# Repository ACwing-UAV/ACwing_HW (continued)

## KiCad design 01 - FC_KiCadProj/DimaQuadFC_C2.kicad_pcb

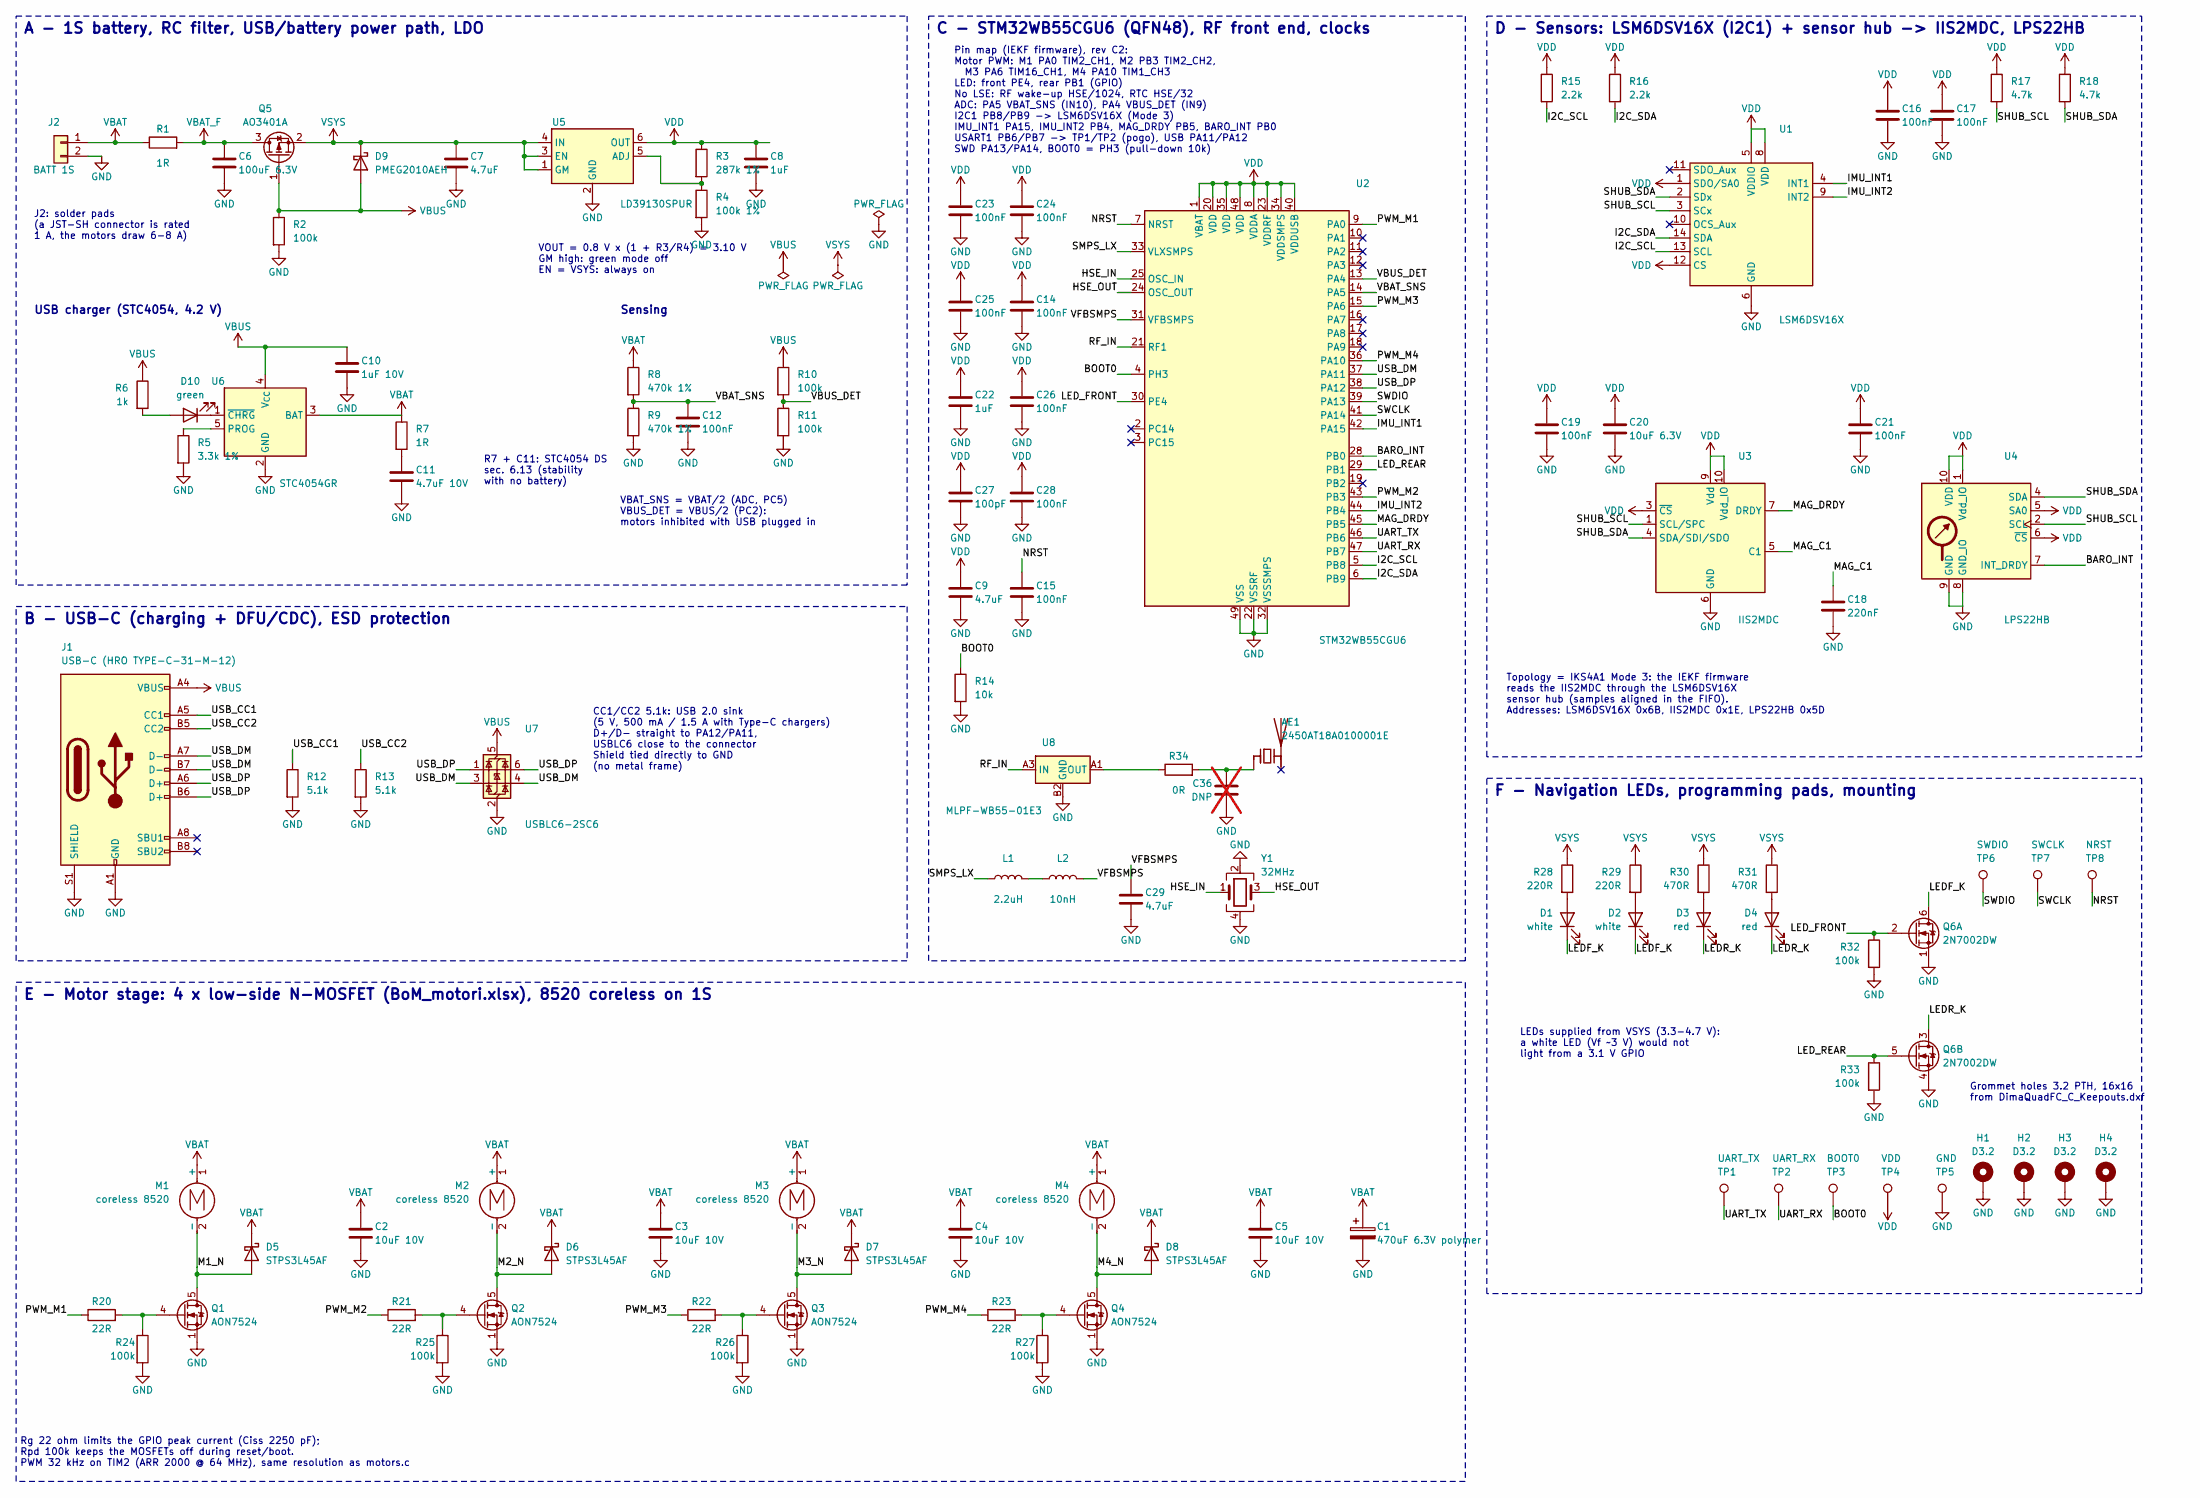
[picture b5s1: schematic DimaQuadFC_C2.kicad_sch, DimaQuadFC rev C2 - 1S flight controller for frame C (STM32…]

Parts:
AE1: 2450AT18A0100001E; Johanson_2450AT18x100
C1: 470uF 6.3V polymer; CP_EIA-7343-31_Kemet-D
C2, C3, C4, C5: 10uF 10V; C_0603_1608Metric
C6: 100uF 6.3V; C_1206_3216Metric
C7, C9: 4.7uF; C_0603_1608Metric
C8, C22: 1uF; C_0402_1005Metric
C10: 1uF 10V; C_0402_1005Metric
C11: 4.7uF 10V; C_0603_1608Metric
C12, C14, C15, C16, C17, C19, C21, C23, C24, C25, C26, C28: 100nF; C_0402_1005Metric
C18: 220nF; C_0402_1005Metric
C20: 10uF 6.3V; C_0603_1608Metric
C27: 100pF; C_0402_1005Metric
C29: 4.7uF; C_0402_1005Metric
C36: DNP; C_0402_1005Metric; not fitted
D1, D2: white; LED_0402_1005Metric
D3, D4: red; LED_0402_1005Metric
D5, D6, D7, D8: STPS3L45AF; D_SMAflat
D9: PMEG2010AEH; D_SOD-123F
D10: green; LED_0402_1005Metric
H1, H2, H3, H4: D3.2; Grommet_PTH_3.2mm_Pad5.0mm
J1: USB-C (HRO TYPE-C-31-M-12); USB_C_Receptacle_HRO_TYPE-C-31-M-12
J2: BATT 1S; BattPads_1x02_SMD
L1: 2.2uH; L_0805_2012Metric
L2: 10nH; L_0402_1005Metric
M1, M2, M3, M4: coreless 8520; MotorPads_1x02_SMD
Q1, Q2, Q3, Q4: AON7524; Vishay_PowerPAK_1212-8_Single
Q5: AO3401A; SOT-23
Q6: 2N7002DW; SOT-363_SC-70-6
R1: 1R; R_0603_1608Metric
R2, R10, R11, R24, R25, R26, R27, R32, R33: 100k; R_0402_1005Metric
R3: 287k 1%; R_0402_1005Metric
R4: 100k 1%; R_0402_1005Metric
R5: 3.3k 1%; R_0402_1005Metric
R6: 1k; R_0402_1005Metric
R7: 1R; R_0402_1005Metric
R8, R9: 470k 1%; R_0402_1005Metric
R12, R13: 5.1k; R_0402_1005Metric
R14: 10k; R_0402_1005Metric
R15, R16: 2.2k; R_0402_1005Metric
R17, R18: 4.7k; R_0402_1005Metric
R20, R21, R22, R23: 22R; R_0402_1005Metric
R28, R29: 220R; R_0402_1005Metric
R30, R31: 470R; R_0402_1005Metric
R34: 0R; R_0402_1005Metric
TP1: UART_TX; TestPoint_Pad_D1.0mm
TP2: UART_RX; TestPoint_Pad_D1.0mm
TP3: BOOT0; TestPoint_Pad_D1.0mm
TP4: VDD; TestPoint_Pad_D1.0mm
TP5: GND; TestPoint_Pad_D1.0mm
TP6: SWDIO; TestPoint_Pad_D1.0mm
TP7: SWCLK; TestPoint_Pad_D1.0mm
TP8: NRST; TestPoint_Pad_D1.0mm
U1: LSM6DSV16X; LGA-14_3x2.5mm_P0.5mm_LayoutBorder3x4y
U2: STM32WB55CGU6; QFN-48-1EP_7x7mm_P0.5mm_EP5.6x5.6mm
U3: IIS2MDC; LGA-12_2x2mm_P0.5mm
U4: LPS22HB; ST_HLGA-10_2x2mm_P0.5mm_LayoutBorder3x2y
U5: LD39130SPUR; DFN-6_1.3x1.2mm_P0.4mm
U6: STC4054GR; TSOT-23-5
U7: USBLC6-2SC6; SOT-23-6
U8: MLPF-WB55-01E3; ST_MLPF-WB55-01E3_CSP-6
Y1: 32MHz; Crystal_SMD_2016-4Pin_2.0x1.6mm

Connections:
BARO_INT: U2.28 (PB0), U4.7 (INT_DRDY)
BOOT0: R14.1, TP3.1, U2.4 (PH3)
GND: C1.2, C2.2, C3.2, C4.2, C5.2, C6.2, C7.2, C8.2, C9.2, C10.2, C11.2, C12.2, C14.2, C15.2, C16.2, C17.2, C18.2, C19.2, C20.2, C21.2, C22.2, C23.2, C24.2, C25.2, C26.2, C27.2, C28.2, C29.2, C36.2, H1.1, H2.1, H3.1, H4.1, J1.A1 (GND), J1.A12 (GND), J1.B1 (GND), J1.B12 (GND), J1.S1 (SHIELD), J2.2, Q1.1 (S), Q1.2 (S), Q1.3 (S), Q2.1 (S), Q2.2 (S), Q2.3 (S), Q3.1 (S), Q3.2 (S), Q3.3 (S), Q4.1 (S), Q4.2 (S), Q4.3 (S), Q6.1 (S), Q6.4 (S), R2.2, R4.2, R5.2, R9.2, R11.2, R12.2, R13.2, R14.2, R24.2, R25.2, R26.2, R27.2, R32.2, R33.2, TP5.1, U1.6 (GND), U1.7 (GND), U2.22 (VSSRF), U2.32 (VSSSMPS), U2.49 (VSS), U3.6 (GND), U3.8 (GND), U4.3 (GND), U4.8 (GND_IO), U4.9 (GND), U5.2 (GND), U6.2 (GND), U7.2 (GND), U8.A2 (GND), U8.B1 (GND), U8.B2 (GND), U8.B3 (GND), Y1.2, Y1.4
HSE_IN: U2.25 (OSC_IN), Y1.1
HSE_OUT: U2.24 (OSC_OUT), Y1.3
I2C_SCL: R15.2, U1.13 (SCL), U2.5 (PB8)
I2C_SDA: R16.2, U1.14 (SDA), U2.6 (PB9)
IMU_INT1: U1.4 (INT1), U2.42 (PA15)
IMU_INT2: U1.9 (INT2), U2.44 (PB4)
LEDF_K: D1.1 (K), D2.1 (K), Q6.6 (D)
LEDR_K: D3.1 (K), D4.1 (K), Q6.3 (D)
LED_FRONT: Q6.2 (G), R32.1, U2.30 (PE4)
LED_REAR: Q6.5 (G), R33.1, U2.29 (PB1)
M1_N: D5.2 (A), M1.2 (-), Q1.5 (D)
M2_N: D6.2 (A), M2.2 (-), Q2.5 (D)
M3_N: D7.2 (A), M3.2 (-), Q3.5 (D)
M4_N: D8.2 (A), M4.2 (-), Q4.5 (D)
MAG_C1: C18.1, U3.5 (C1)
MAG_DRDY: U2.45 (PB5), U3.7 (DRDY)
NRST: C15.1, TP8.1, U2.7 (NRST)
unnamed: AE1.1 (FEED), C36.1, R34.2
unnamed: C11.1, R7.2
unnamed: D1.2 (A), R28.2
unnamed: D2.2 (A), R29.2
unnamed: D3.2 (A), R30.2
unnamed: D4.2 (A), R31.2
unnamed: D10.2 (A), R6.2
unnamed: D10.1 (K), U6.1 (~CHRG)
unnamed: L1.2, L2.1
unnamed: Q1.4 (G), R20.2, R24.1
unnamed: Q2.4 (G), R21.2, R25.1
unnamed: Q3.4 (G), R22.2, R26.1
unnamed: Q4.4 (G), R23.2, R27.1
unnamed: R3.2, R4.1, U5.5 (ADJ)
unnamed: R5.1, U6.5 (PROG)
unnamed: R34.1, U8.A1 (OUT)
PWM_M1: R20.1, U2.9 (PA0)
PWM_M2: R21.1, U2.43 (PB3)
PWM_M3: R22.1, U2.15 (PA6)
PWM_M4: R23.1, U2.36 (PA10)
RF_IN: U2.21 (RF1), U8.A3 (IN)
SHUB_SCL: R17.2, U1.3 (SCx), U3.1 (SCL/SPC), U4.2 (SCL)
SHUB_SDA: R18.2, U1.2 (SDx), U3.4 (SDA/SDI/SDO), U4.4 (SDA)
SMPS_LX: L1.1, U2.33 (VLXSMPS)
SWCLK: TP7.1, U2.41 (PA14)
SWDIO: TP6.1, U2.39 (PA13)
UART_RX: TP2.1, U2.47 (PB7)
UART_TX: TP1.1, U2.46 (PB6)
USB_CC1: J1.A5 (CC1), R12.1
USB_CC2: J1.B5 (CC2), R13.1
USB_DM: J1.A7 (D-), J1.B7 (D-), U2.37 (PA11), U7.3 (I/O2), U7.4 (I/O2)
USB_DP: J1.A6 (D+), J1.B6 (D+), U2.38 (PA12), U7.1 (I/O1), U7.6 (I/O1)
VBAT: C1.1, C2.1, C3.1, C4.1, C5.1, D5.1 (K), D6.1 (K), D7.1 (K), D8.1 (K), J2.1, M1.1 (+), M2.1 (+), M3.1 (+), M4.1 (+), R1.1, R7.1, R8.1, U6.3 (BAT)
VBAT_F: C6.1, Q5.3 (D), R1.2
VBAT_SNS: C12.1, R8.2, R9.1, U2.14 (PA5)
VBUS: C10.1, D9.2 (A), J1.A4 (VBUS), J1.A9 (VBUS), J1.B4 (VBUS), J1.B9 (VBUS), Q5.1 (G), R2.1, R6.1, R10.1, U6.4 (V_{CC}), U7.5 (VBUS)
VBUS_DET: R10.2, R11.1, U2.13 (PA4)
VDD: C8.1, C9.1, C14.1, C16.1, C17.1, C19.1, C20.1, C21.1, C22.1, C23.1, C24.1, C25.1, C26.1, C27.1, C28.1, R3.1, R15.1, R16.1, R17.1, R18.1, TP4.1, U1.1 (SDO/SA0), U1.5 (VDDIO), U1.8 (VDD), U1.12 (CS), U2.1 (VBAT), U2.8 (VDDA), U2.20 (VDD), U2.23 (VDDRF), U2.34 (VDDSMPS), U2.35 (VDD), U2.40 (VDDUSB), U2.48 (VDD), U3.3 (~CS), U3.9 (Vdd), U3.10 (Vdd_IO), U4.1 (Vdd_IO), U4.5 (SA0), U4.6 (~CS), U4.10 (VDD), U5.6 (OUT)
VFBSMPS: C29.1, L2.2, U2.31 (VFBSMPS)
VSYS: C7.1, D9.1 (K), Q5.2 (S), R28.1, R29.1, R30.1, R31.1, U5.1 (GM), U5.3 (EN), U5.4 (IN)

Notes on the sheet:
A - 1S battery, RC filter, USB/battery power path, LDO
VOUT = 0.8 V x (1 + R3/R4) = 3.10 V GM high: green mode off EN = VSYS: always on
J2: solder pads (a JST-SH connector is rated 1 A, the motors draw 6-8 A)
USB charger (STC4054, 4.2 V)
R7 + C11: STC4054 DS sec. 6.13 (stability with no battery)
Sensing
VBAT_SNS = VBAT/2 (ADC, PC5) VBUS_DET = VBUS/2 (PC2): motors inhibited with USB plugged in
B - USB-C (charging + DFU/CDC), ESD protection
CC1/CC2 5.1k: USB 2.0 sink (5 V, 500 mA / 1.5 A with Type-C chargers) D+/D- straight to PA12/PA11, USBLC6 close to the connector Shield tied directly to GND (no metal frame)
C - STM32WB55CGU6 (QFN48), RF front end, clocks
Pin map (IEKF firmware), rev C2: Motor PWM: M1 PA0 TIM2_CH1, M2 PB3 TIM2_CH2, M3 PA6 TIM16_CH1, M4 PA10 TIM1_CH3 LED: front PE4, rear PB1 (GPIO) No LSE: RF wake-up HSE/1024, RTC HSE/32 ADC: PA5 VBAT_SNS (IN10), PA4 VBUS_DET (IN9) I2C1 PB8/PB9 -> LSM6DSV16X (Mode 3) IMU_INT1 PA15, IMU_INT2 PB4, MAG_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
D - Sensors: LSM6DSV16X (I2C1) + sensor hub -> IIS2MDC, LPS22HB
Topology = IKS4A1 Mode 3: the IEKF firmware reads the IIS2MDC through the LSM6DSV16X sensor hub (samples aligned in the FIFO). Addresses: LSM6DSV16X 0x6B, IIS2MDC 0x1E, LPS22HB 0x5D
E - Motor stage: 4 x low-side N-MOSFET (BoM_motori.xlsx), 8520 coreless on 1S
Rg 22 ohm limits the GPIO peak current (Ciss 2250 pF); Rpd 100k keeps the MOSFETs off during reset/boot. PWM 32 kHz on TIM2 (ARR 2000 @ 64 MHz), same resolution as motors.c
F - Navigation LEDs, programming pads, mounting
LEDs supplied from VSYS (3.3-4.7 V): a white LED (Vf ~3 V) would not light from a 3.1 V GPIO
Grommet holes 3.2 PTH, 16x16 from DimaQuadFC_C_Keepouts.dxf

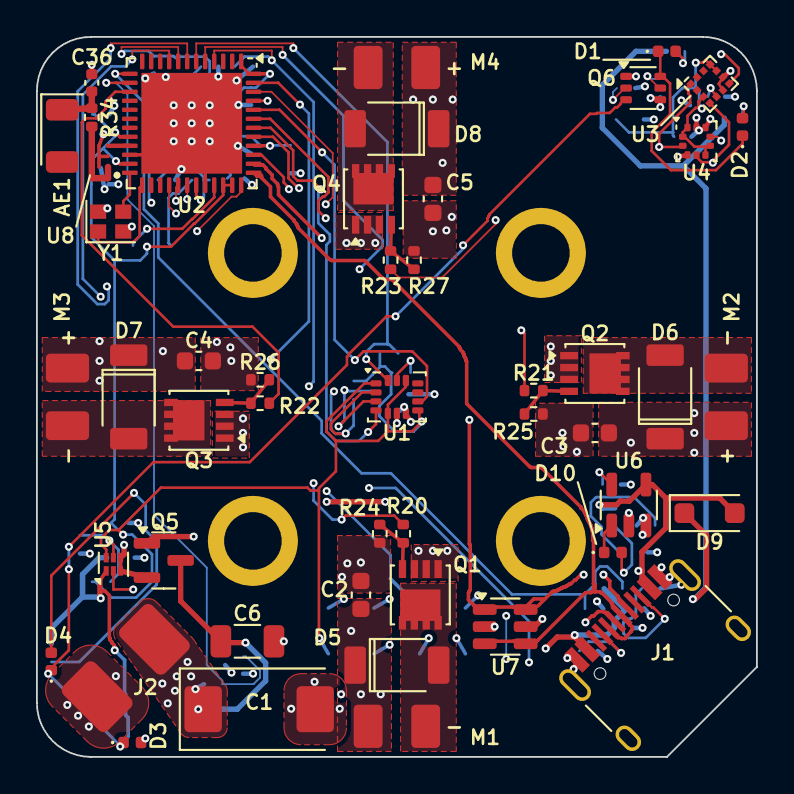
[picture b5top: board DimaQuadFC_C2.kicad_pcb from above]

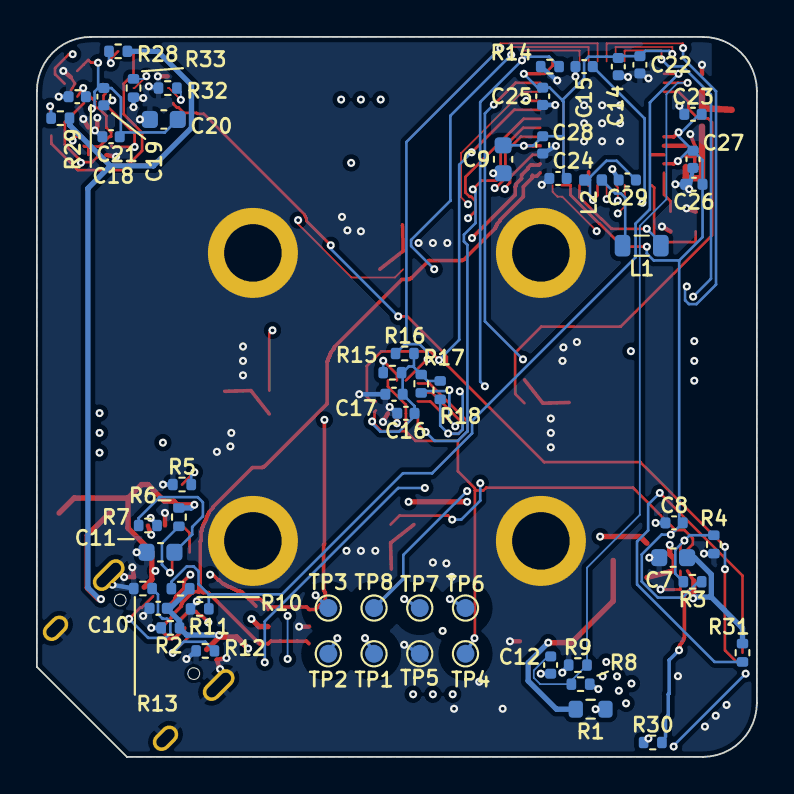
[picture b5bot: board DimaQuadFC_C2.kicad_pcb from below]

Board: 4 copper layers, 40.0 x 40.0 mm, 108 parts (56 on the bottom side), 60 nets.

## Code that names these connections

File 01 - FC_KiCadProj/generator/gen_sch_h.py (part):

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
# VREG: output of the input buck U12 (lower part of this block): 4.1 V from 2S-6S, about VBAT on 1S (100% duty cycle)
sch.wire((25.4, Y0), (55.88, Y0))
sch.label('VREG', (25.4, Y0), 180)
node('VREG', (35.56, Y0))
C('C6', '100uF 6.3V', 45.72, Y0 + 3.81, ('W', 'VREG'), 'GND', fp=FP_C1206,
  fields={'Note': 'Buck output (LM5166 PFM, ILIM 1.25 A: COUT >= 50 L Ipk^2 / VOUT^2 ~ 100 uF), with C46'})
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         fields={'Note': 'Sunlord SWPA5040S220MT, 22 uH, Isat 1.9 A, 168 mOhm, 5 x 5 x 4 mm (PFM: L >= (VIN - VOUT) x 260 ns / 0.35 A at 25 V)'},
         field_pos={'Reference': (sw[0] + 8.89, sw[1] - 3.81), 'Value': (sw[0] + 8.89, sw[1] + 3.81)})
sch.wire(sw, sch.pin_end('L3', '1')[0])
sch.label('BUCK_SW', (sw[0] + 2.54, sw[1]), 0)
lo = sch.pin_end('L3', '2')[0]
sch.wire(lo, (lo[0] + 27.94, lo[1]))
sch.label('VREG', (lo[0] + 27.94, lo[1]), 0)
C('C46', '22uF 25V', lo[0] + 20.32, lo[1] + 3.81, ('W', 'VREG'), 'GND', fp='Capacitor_SMD:C_0805_2012Metric',
  fields={'Note': 'Buck output, X5R 0805, next to L3 / U12 (with C6)'})
sch.junction((lo[0] + 20.32, lo[1]))
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R('R47', '470k 1%', lo[0] + 5.08, fb[1] - 3.81, ('W', 'VREG'), ('W', 'BUCK_FB'), fields={'Note': 'VREG = 1.223 V x (1 + 470k/200k) = 4.10 V'})
R('R48', '200k 1%', lo[0] + 5.08, fb[1] + 3.81, ('W', 'BUCK_FB'), 'GND')
sch.wire(fb, (lo[0] + 5.08, fb[1])); sch.junction((lo[0] + 5.08, fb[1]))
sch.label('BUCK_FB', (fb[0] + 2.54, fb[1]), 0)
sch.wire((lo[0] + 5.08, lo[1]), (lo[0] + 5.08, fb[1] - 7.62)); sch.junction((lo[0] + 5.08, lo[1]))
C('C47', '4.7uF 50V', 20.32, 90.17, 'VBAT', 'GND', fp=FP_C1206, side='left',
  fields={'Note': 'Buck input, X7R 50 V 1206, at the VIN / GND pins (6S: 25.2 V)'})
C('C49', '10nF', 30.48, 90.17, 'VBAT', 'GND', side='left', fields={'Note': 'Buck input HF bypass, X7R 50 V, closest to VIN'})
note('VBAT 1S-6S (3.0-25.2 V), from ESC A J2 pin 2\n(JST SH 8-pin, as on commercial FC/ESC stacks).\nVREG 4.1 V (2S-6S), VBAT - drop (1S).\nLoad on VREG <= 0.5 A', (66.04, 100.33))

# Sense: battery voltage and USB presence
sch.text('Sensing', (124.46, 66.04), size=1.5, bold=True)
divider('R8', 'R9', '100k 1%', '10k', 127.0, 76.2, 'VBAT', 'VBAT_SNS', 'GND', cref='C12', label_dx=15.24)
divider('R10', 'R11', '100k', '100k', 154.94, 76.2, 'VBUS', 'VBUS_DET', 'GND', label_dx=5.08)
note('VBAT_SNS = VBAT x 10/110 (ADC PA5, IN10):\n25.2 V (6S) -> 2.29 V, full scale 34 V\nVBUS_DET = VBUS/2 (GPIO PB1):\nmotors inhibited with USB plugged in', (124.46, 101.6))

# ================================================================ B. USB-C
block('B - USB-C (DFU/CDC, bench supply; no charger), ESD protection', (12, 122), (178, 188))
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         {'1': 'USB_DP', '6': 'USB_DP', '3': 'USB_DM', '4': 'USB_DM', '5': 'VBUS', '2': 'GND'},
         field_pos={'Reference': (106.68, 144.78), 'Value': (106.68, 162.56), 'just': 'left'})
note('CC1/CC2 5.1k: USB 2.0 sink\n(5 V, 500 mA / 1.5 A with Type-C chargers)\n'
     'D+/D- straight to PA12/PA11,\nUSBLC6 close to the connector\n'
     'Shield tied directly to GND\n(no metal frame)', (119.38, 140.97))

# ================================================================ C. MCU (rev C2: STM32WB55CGU6 QFN48 + RF front end)
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    '4': 'BOOT0', '7': 'NRST',
    # rev F pin map (ACwing_FC_A_pinmap.md): the MCU sits at the board centre, no pin row faces an edge.
    # All four motor outputs on TIM2 CH1-CH4 (one DMA burst: PWM for brushed, DShot / bidirectional DShot for brushless)
    '9': 'PWM_M1', '10': 'PWM_M2', '11': 'PWM_M3', '12': 'PWM_M4',   # PA0-PA3 TIM2_CH1-CH4
    '13': 'ESC_CUR',                                   # PA4 ADC1_IN9: current from the ESC link (0.1 V/A on DimaQuadESC)
    '14': 'VBAT_SNS',                                  # PA5 ADC1_IN10: VBAT/2
    '29': 'VBUS_DET',                                  # PB1 GPIO: VBUS/2 reads high with USB plugged in
    '43': 'SPI_SCK', '44': 'SPI_MISO', '45': 'SPI_MOSI',   # PB3/PB4/PB5 SPI1: IMU + log flash
    '2': 'IMU_CS', '30': 'FLASH_CS',                   # PC14 (east side, next to the IMU; GPIO, 2 MHz is plenty for a CS), PE4
    '17': 'PWM_M5', '18': 'PWM_M6', '36': 'PWM_M7',    # PA8/PA9/PA10 TIM1_CH1-CH3 (DMA): motors M5-M7 -> ESC link B J6 (rev H)
    '15': 'PWM_M8',                                    # PA6 TIM16_CH1 (DMA): motor M8 -> J6 (rev H)
    '16': 'RGB_DIN',                                   # PA7 TIM17_CH1 (DMA): 4 x WS2812B (rev H, was PB6)
    '46': 'CRSF_TX', '47': 'CRSF_RX',                  # PB6/PB7 USART1 (alternate pins) -> ELRS receiver J5 (rev H, was PA9/PA10)
    '28': 'ESC_TLM_MCU',                               # PB0 GPIO/EXTI: ESC A serial telemetry, optional (rev H, was PB7)
    '5': 'I2C_SCL', '6': 'I2C_SDA',                    # PB8/PB9 I2C1: expansion bus (Qwiic J3) only
    '37': 'USB_DM', '38': 'USB_DP',                    # PA11/PA12 USB FS
    '39': 'SWDIO', '41': 'SWCLK',                      # PA13/PA14
    '42': 'IMU_INT1',                                  # PA15
    '3': None, '19': None,                             # PC15 (no LSE), PB2 free
}
sch.part('U2', 'MCU_ST_STM32WB:STM32WB55CGUx', 'STM32WB55CGU6', MX, MY, 0, mcu,
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sch.tie('U2', ['1', '20', '35', '48', '8', '23', '34', '40'], 'VDD')
sch.tie('U2', ['22', '49', '32'], 'GND', sym_at=1)
note('Pin map (IEKF firmware), rev A:\n'
     'Motors M1-M4 PA0-PA3 TIM2_CH1-CH4 -> ESC A J2; M5-M7 PA8-PA10 TIM1_CH1-CH3, M8 PA6 TIM16_CH1 -> ESC B J6\n'
     '(PWM 32 kHz brushed / DShot, bidirectional DShot: every motor timer has DMA)\n'
     'ADC: PA4 ESC_CUR (IN9), PA5 VBAT_SNS (IN10, x10/110); ESC A serial telemetry PB0 (optional)\n'
     'SPI1 PB3 SCK / PB4 MISO / PB5 MOSI: IMU (CS PC14) + log flash (CS PE4), IMU_INT1 PA15\n'
     'USART1 PB6 TX / PB7 RX -> ELRS (CRSF 420 kbaud), J5\n'
     'I2C1 PB8/PB9 -> expansion bus (Qwiic J3 + J4: GPS board, flow board, sensors)\n'
     'RGB LEDs PA7 (TIM17_CH1 + DMA, buffer U13, 4 x XL-2020); VBUS_DET PB1; PB2 free\n'
     'No LSE: RF wake-up HSE/1024, RTC HSE/32. USB PA11/PA12 (DFU, CDC)\n'
     'SWD PA13/PA14, BOOT0 = PH3 (pull-down 10k)', (186.69, 17.78))

# decoupling (one 100 nF per supply pin, VDDA 1 uF, VDDRF 100 nF + 100 pF), row under the MCU
DEC = [('C23', '100nF', FP_C, 'VDD pin 20'), ('C24', '100nF', FP_C, 'VDD pin 35'), ('C25', '100nF', FP_C, 'VDD pin 48 / VBAT pin 1'),
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
# HSE 32 MHz (internal trimming caps, no external load caps)
sch.part('Y1', 'Device:Crystal_GND24', '32MHz', 240.03, 175.26, 0,
         {'1': 'HSE_IN', '3': 'HSE_OUT', '2': 'GND', '4': 'GND'}, fp='Crystal:Crystal_SMD_2016-4Pin_2.0x1.6mm',
         fields={'Note': 'NDK NX2016SA 32 MHz (DS13252 table 5); load caps integrated in the MCU (trimmed in firmware)'},
         field_pos={'Reference': (243.84, 168.91), 'Value': (243.84, 171.45), 'just': 'left'})
# no LSE crystal: BLE RF wake-up clock = HSE/1024, RTC = HSE/32 (pins 2/3 PC14/PC15 not connected)

# RF: RF1 -> MLPF-WB55-01E3 -> pi network (tuning) -> chip antenna
sch.part('U8', LIB + ':MLPF-WB55-01E3', 'MLPF-WB55-01E3', 207.01, 152.4, 0, {'A3': 'RF_IN', 'A1': ('W', 'RF_ANT'), 'B2': 'GND'},
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         fields={'Note': 'IIS2MDCTR (industrial grade of the LIS2MDL: same LGA-12 pinout and registers). Front corner, farthest from battery and motor currents. No motor current under it'},
         field_pos={'Reference': (332.74, 93.98), 'Value': (332.74, 124.46), 'just': 'left'})
sch.tie('U3', ['9', '10'], 'VDD', sym_at=0)
C('C18', '220nF', 350.52, 121.92, 'MAG_C1', 'GND', fields={'Note': 'IIS2MDC C1: 220 nF, ESR < 200 mOhm, close to pins 5-6'})
C('C19', '100nF', 297.18, 88.9, 'VDD', 'GND')
C('C20', '10uF 6.3V', 309.88, 88.9, 'VDD', 'GND', fp=FP_C0603, fields={'Note': 'IIS2MDC DS: 100 nF + 10 uF on Vdd'})

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         {'1': ('W', 'GND'), '2': ('W', 'VBAT'), '3': ('W', 'ESC_CUR_IN'), '4': ('W', 'ESC_TLM'),
          '5': ('W', 'ESC_M1'), '6': ('W', 'ESC_M2'), '7': ('W', 'ESC_M3'), '8': ('W', 'ESC_M4')},
         fp='Connector_JST:JST_SH_SM08B-SRSS-TB_1x08-1MP_P1.00mm_Horizontal', mirror=True,
         fields={'Note': 'ESC link A, JST SH 8-pin side entry, top side, rear edge: 1 GND, 2 VBAT (1S-6S, FC supply), 3 CUR, 4 TLM, 5-8 M1-M4. 1:1 cable. Check the pinout of a third-party ESC'},
         field_pos={'Reference': (36.83, EY + 1.27), 'Value': (36.83, EY + 3.81), 'just': 'right'})
pins = {n: sch.pin_end('J2', n)[0] for n in '12345678'}
# fan-out: the 2.54 mm pin rows open up to 7.62 mm rows (jog x decreases with the pin number: no crossings)
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    sch.label(net, (66.04, y), 0)
    sch.part(ref, 'Device:R', '1k' if n == '3' else '100R', 76.2, y, 90, {'1': ('W', net), '2': ('W', mcu_net)}, fp=FP_R,
             fields={'Note': {'3': 'ADC input protection: limits the injected current if an ESC drives CUR above 3.3 V; RC with C1',
                              '4': 'Series resistor, ESC serial telemetry input to PB0 (optional; EDT on the motor lines preferred)'}.get(n, 'Series resistor on the cable line (edge rate, ESD, a fault on the ESC side)')},
             field_pos={'Reference': (76.2, y - 2.54), 'Value': (76.2, y + 2.54)})
    sch.wire(sch.pin_end(ref, '2')[0], (88.9, y))
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
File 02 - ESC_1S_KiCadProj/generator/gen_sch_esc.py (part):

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def flag_label(net, p, n):
    sch._instance('power:PWR_FLAG', '#FLG%02d' % n, 'PWR_FLAG', p[0], p[1], 0)
    sch.label(net, p, 0)
flag_label('VBAT_RAW', (30.48, 25.4), 10)
flag_label('VBAT_SH', (66.04, 25.4), 11)
note('Battery current: CUR = 0.1 V/A on J1 pin 3 (FC ADC PA4); discharge only.\n'
     'Motor peak about 8 A -> 0.8 V; full scale 31 A at 3.1 V.\n'
     'Shunt loss at 6 A: 72 mW. U1 senses R9 through two Kelvin tracks.', (15.24, 72.39))

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sch.part('J1', 'Connector_Generic:Conn_01x08', 'ESC link', 172.72, 38.1, 0,
         {'1': 'GND', '2': 'VBAT', '3': 'CUR', '4': None, '5': 'PWM_M1', '6': 'PWM_M2', '7': 'PWM_M3', '8': 'PWM_M4'},
         fp='Connector_JST:JST_SH_SM08B-SRSS-TB_1x08-1MP_P1.00mm_Horizontal',
         fields={'Note': 'JST SH 8-pin side entry, top side, rear-right edge: 1 GND, 2 VBAT, 3 CUR, 4 TLM (n.c.), 5-8 M1-M4. 1:1 cable to the FC'},
         field_pos={'Reference': (168.91, 25.4), 'Value': (168.91, 52.07), 'just': 'left'})
note('Common 4-in-1 ESC pinout. A brushless 20 x 20 1S 4-in-1 ESC plugs into the\n'
     'same FC cable: check its pinout first (some vendors swap VBAT/GND or CUR/TLM).\n'
     'TLM (pin 4) is not used by this brushed board.\n'
     'VBAT on pin 2 also supplies the whole FC (up to 0.5 A at 4.1 V).\n'
     'VBAT is off while the charge port is plugged in (Q5): FC and motors off.', (190.5, 30.48))
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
